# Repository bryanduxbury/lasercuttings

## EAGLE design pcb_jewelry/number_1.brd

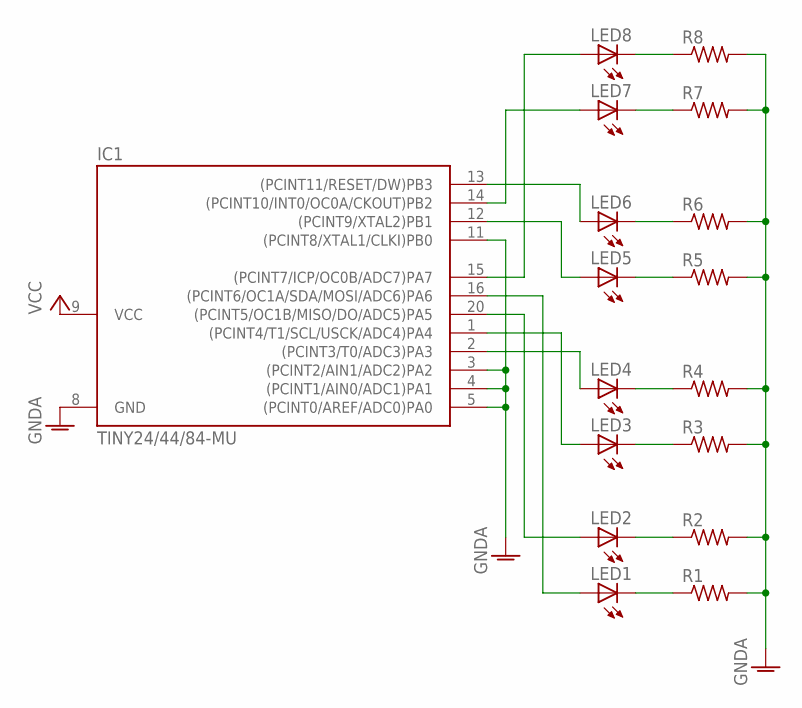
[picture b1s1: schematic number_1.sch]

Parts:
IC1: TINY24/44/84-MU; QFN/MLF20
LED1, LED2, LED3, LED4, LED5, LED6, LED7, LED8: LEDCHIP-LED0603; CHIP-LED0603
R1, R2, R3, R4, R5, R6, R7, R8: R-US_R0603; R0603

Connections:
GNDA: IC1.3 ((PCINT2/AIN1/ADC2)PA2), IC1.4 ((PCINT1/AIN0/ADC1)PA1), IC1.5 ((PCINT0/AREF/ADC0)PA0), IC1.8 (GND), IC1.11 ((PCINT8/XTAL1/CLKI)PB0), R1.2, R2.2, R3.2, R4.2, R5.2, R6.2, R7.2, R8.2
unnamed: IC1.16 ((PCINT6/OC1A/SDA/MOSI/ADC6)PA6), LED1.A
unnamed: IC1.20 ((PCINT5/OC1B/MISO/DO/ADC5)PA5), LED2.A
unnamed: IC1.1 ((PCINT4/T1/SCL/USCK/ADC4)PA4), LED3.A
unnamed: IC1.2 ((PCINT3/T0/ADC3)PA3), LED4.A
unnamed: IC1.15 ((PCINT7/ICP/OC0B/ADC7)PA7), LED8.A
unnamed: IC1.14 ((PCINT10/INT0/OC0A/CKOUT)PB2), LED7.A
unnamed: IC1.13 ((PCINT11/RESET/DW)PB3), LED6.A
unnamed: IC1.12 ((PCINT9/XTAL2)PB1), LED5.A
unnamed: LED7.C, R7.1
unnamed: LED8.C, R8.1
unnamed: LED6.C, R6.1
unnamed: LED5.C, R5.1
unnamed: LED4.C, R4.1
unnamed: LED3.C, R3.1
unnamed: LED2.C, R2.1
unnamed: LED1.C, R1.1
VCC: IC1.9 (VCC)

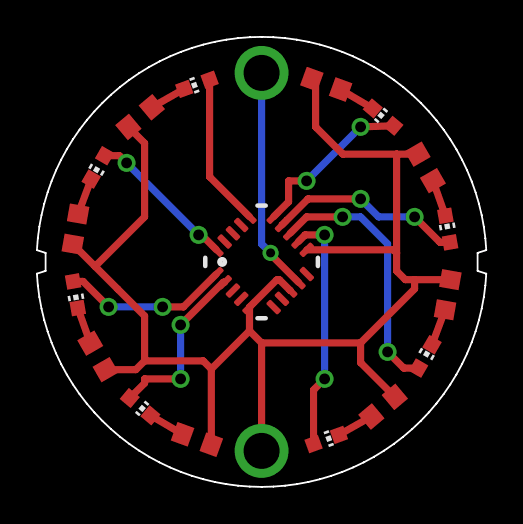
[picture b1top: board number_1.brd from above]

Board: 2 copper layers, 25.0 x 25.0 mm, 17 parts (0 on the bottom side), 17 nets.

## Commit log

2011-09-03 owl clock import
2011-09-03 let's etch some chocolate homies
2011-09-03 color for cutting
2011-09-04 adjust size of the etched letters
2011-09-05 first crack at a stylized tree-like earring design
2011-09-06 aha, something genevieve said she'd wear
2011-09-06 move stuff into earrings subdir
2011-09-06 ak47 earrings
2011-09-13 script for generating overlapping randomized boxes wall art thingy and first one done all the way.
2011-09-17 starting on the tree lamp
2011-09-20 initial schematic/board for tree lamp project
2011-09-22 layout for capacitive pads experiment, plus some soic breakout boards :)
2011-09-22 add a second rectangles drawing and adjust the first one for easy cutting
2011-09-22 playing around with the tree lamp circuit board design
2011-09-23 some minor progress
2011-09-23 adjustments to boxes.rb to give mostly attractive designs
2011-09-24 another wall art example
2011-09-24 move the rect wall art stuff down into a subdir
2011-09-27 lots of changes to commit
2011-09-27 add mounting/sandwiching holes
2011-09-28 even more ready to cut...
2011-09-29 wait, don't waste all that copper...
2011-09-29 make the head of the pressfit piece sharper
2011-09-29 narrow down the tail portion of the arrowhead
2011-10-04 updates to the boxes script to make some good stuff happen
2011-10-04 all of the designs i want to cut
2011-10-04 sketch of a design for a laser cut bearing
2011-10-04 small changes to the press fit test
2011-10-04 move tree lamp stuff into subdir
2011-10-04 make a mechanical subdir
2011-10-04 move capacitive pads into tree lamp project (where it belongs)
2011-10-04 remove comments from boxer script
2011-10-11 -first draft of smb ? block lamp box -second tree lamp board schematic, now with integral sensor
2012-03-12 outstanding stuff from forever ago
2012-03-25 makin' progress
2012-03-26 more incremental progress
2012-04-06 woohoo, simulation more or less working
2012-04-06 tons of progress on the 4-bar simulation math
2012-04-08 lots of adjustments made, have bottom of the box panelized
2012-04-08 same as prior message
2012-05-06 gen's jewelry box
2012-05-06 cake topper
2012-05-06 all panelized up
2012-05-06 fix a lot of lines
2012-05-27 move stock images down a level
2012-05-27 don't need a static render checked in
2012-06-10 some decorations to cut out
2012-06-10 mods to the box; make panelized versions that don't require hand-modification at the last minute
2012-06-10 clean up a bunch of intermediate files
2012-06-21 basic shape of tray
2012-06-22 many cutouts on top side squared away
2012-06-23 tray 2 ready to rock
2012-06-23 some polishing / panelization on tray 1
2012-06-23 yay for tray3
2012-06-23 added tray4
2012-06-25 shrink tray4 back to normal size
2012-06-25 first draft of shadow box things
2012-06-25 started laying out vector mapper project
2012-07-25 work around the weird issue with busted paths
2012-08-01 holy crap, i haven't committed this yet?
2012-08-02 getting the panelized version working
2012-08-04 clean up some unused files; more improvements to design
2012-08-06 support scaling independent of adjustment"
2012-08-06 cleanup and adjustments
2012-08-07 hexagonal coaster design
2012-08-08 figured out a reliable way to make hexagon blanks. gutter adjustments now work the way they're supposed to.
2012-08-08 failed, but worth remembering some of the crazy math
2012-08-08 etched flower earring design
2012-08-08 make the inner circle smoother
2012-08-09 some adjustments
2012-08-09 corner clamp design draft
2012-08-09 design for circular arrow earring
2012-08-09 circular arrows svg design
2012-08-09 ginkgo earrings
2012-08-10 first draft of foldable interlocking blocks
2012-08-25 starwars coasters
2012-08-25 improvements to corner clamp design
2012-08-25 don't lose the diagonal fold helper
2012-08-25 etch the supports instead of using alignment marks
2012-08-25 panelized version of the hex coasters
2012-08-25 earrings collateral
2012-08-25 panelized corner clamps
2012-08-25 planetary gears experiment
2012-08-25 raised flower earrings design
2012-09-04 cuttable/etchable falcon
2012-09-04 some gear stuff
2012-09-04 some slight dimension adjustments
2012-09-24 ali's coasters
2012-09-24 business card attempt #1
2012-09-24 a little work exploring generating a hyperbolic caltrop (lamp?)
2012-09-24 a simple go stading go board design
2012-09-24 well, it's not really a mockup if i can go cut it
2012-09-24 scadfiles for the first few toroidal go board ideas i had
2012-09-24 just getting started... something to finish another day
2012-10-02 roughed in all the panels
2012-10-03 got some of the tab-togethers working
2012-10-03 tabs between the top and fridge-right
2012-10-04 lots of progress on tabbing
2012-10-04 almost everything above the feet tabbed in correctly
2012-10-04 starting to get the bottom + feet all figured out
2012-10-04 working out the bottom connections
2012-10-05 as tabbed-together as its ever gonna be
2012-10-19 lots of marginal improvements; added a door to the oven
2012-10-19 put a door on the sink cupboard
2012-10-19 booya, nice rounded door handles for the fridge
2012-10-19 slot the fridge handles into place
2012-10-20 round out the stove door handle
2012-10-20 tab the stove handle into the door
2012-10-23 work out the rest of the microwave door and handle
2012-10-23 add helpful plane specifiers so that colors are consistent; strip out the manual color specifiers
2012-10-23 starting to work through using plane specifiers for rotation, too
2012-10-26 cleaning up some fallout from plane specifiers
2012-10-26 looks like we're back to sanity
2012-11-05 revisions to go board for a v2
2012-11-05 copy v2->v3
2012-11-06 serious revamping to v3; starting to lay groundwork for through changes
2012-11-06 drawers all sorted out
2012-11-13 moving towards square drawers
2012-11-21 huge bunch of improvements, including hinge cuts
2012-11-21 the final starwars coasters
2012-11-21 incremental improvements on v3 board
2012-11-21 script for generating tray liners
2012-11-21 lasercut hanging shelf FTW
2012-12-05 update dimensions on kids kitchen
2012-12-05 some draft thoughts on the big odometer
2012-12-05 decent looking mockup
2012-12-07 lots of progress
2012-12-07 figured out the bottom dimensions
2012-12-08 created the motor mount bracket (amongst other things)
2012-12-10 LOADS of progress
2012-12-10 lots of changes
2012-12-11 prepping to cut case
2012-12-11 more prep for cutting
2012-12-12 adjustments to the drive gear
2012-12-12 some print statements for dimensions
2012-12-12 lots of adjustments pre-cutting
2012-12-19 quickie first attempt at burrito push pop
2012-12-23 add arduino sketch for controlling motor speed
2012-12-25 working through alternative motor speed controller
2012-12-29 refactor towards a step-based approach for the firmware
2012-12-29 sketch to try out the step based approach (and measure the motor coast)
2013-01-12 experimenting with roller detent idea
2013-01-12 improvments to the gear gen script
2013-01-12 init commit of more traditional counter gears
2013-01-12 measurements of pipe fittings for odometer mounting:
2013-01-13 add a gitignore
2013-01-13 small version of the kitchen for testing purposes
2013-01-13 kitchen scale model panelized
2013-01-13 -experiment with tagging non-leaf modules
2013-01-13 panelized demo counter gears (flat version)
2013-01-13 init commit of uptime project
2013-01-13 rename odometer for convenience's sake
2013-02-04 progress on new rev of tree lamp
2013-02-05 making progress
2013-02-15 improvements
2013-02-19 start on polished odometer design
2013-02-19 adjust size of rebel coaster
2013-02-19 final dimensions of the kids kitchen
2013-02-19 modifications to the original odometer to get the last few parts i need
2013-02-19 increase speed of the motor
2013-02-19 keychain first draft
2013-02-19 all the svgs of coasters + panels thereof
2013-02-25 line up the cutout and the actual outline
2013-02-25 started working on a totally vectorized falcon
2013-02-25 trash the odometer (moved to a separate repo)
2013-08-21 yay nyixie project
2013-08-21 added a bunch of the blank parts
2013-08-21 lots of progress laying out features
2013-08-21 fixed box sides are now jointed together
2013-08-22 power plug set, inside drawer framed
2013-08-22 added some todos
2013-08-22 incremental progress
2013-08-22 exported faceplate for cutting
2013-08-23 added the voltage plate
2013-08-23 fix the hole pattern for the probe plug; add some todos
2013-08-23 added a todo
2013-08-23 placed a beaglebone black footprint
2013-08-26 tonights cuttings
2013-08-26 local mods
2013-08-26 minor changes
2013-08-26 kerf adjust some stuff, screw holes in the back for holding the drawer in, export a lot of the pieces
2013-09-14 add quad and penta designs
2013-09-14 generalized polycircle earrings
2013-09-18 updates to polycircles
2013-09-18 bunch of earring designs that weren't pushed
2013-09-18 ignore eagle temp files
2013-09-20 hex tile draft
2013-09-20 bunch of random stuff
2013-09-20 new design
2013-09-22 outstanding changes
2014-01-23 random earring idea
2014-03-07 add init commit of box project
2014-03-08 fix corner roundness
2014-03-09 added feet to the bottom of the box
2014-03-19 change the sizes of the box again
2014-05-11 set up to export stls
2014-05-11 all sorts of changes to get over the finish line
2014-05-12 init commit of (now obsolete) v1, progress on frame of v2
2014-05-12 shortened some pipes and added in tees and elbows
2014-05-13 sooo many changes, but coming together nicely
2014-05-13 added lower side pegboards and fixed some pipe length stuff
2014-05-13 whitespace
2014-05-20 figured out the pipe-desk bracket situation
2014-05-20 designed better desktop cutouts for the vertical pipes
2014-05-20 added a bunch of TODOs to the header
2014-05-21 adjust some measurements, model the bolt hole in the elbows
2014-05-21 cleaned up dead code, shortened some pipes
2014-05-23 clean up more random lengths
2014-05-23 script to compute optimal pipe cuts
2014-05-27 fix all the bad lengths; handle a bunch of todos
2014-05-27 clear some todos
2014-05-27 initial commits on jewelry tree for gen (dead end?)
2014-05-28 mounting holes galore
2014-06-01 woohoo falcons panel is back
2014-06-01 added modules for clamp drilling jig
2014-06-04 improvements to drilling jig
2014-06-06 panelized the top shelf, drilling jig and an array of clamps
2014-06-09 prep for cutting
2014-07-17 finished with the workbench
2015-01-01 add whale keychain svg
2015-01-23 baby gate holder
2015-01-29 simple cnc-able stand for 20x4 LCD display
2015-03-03 rack for compartment organizers
2015-07-06 initial commit of soldering cart / cabinet
